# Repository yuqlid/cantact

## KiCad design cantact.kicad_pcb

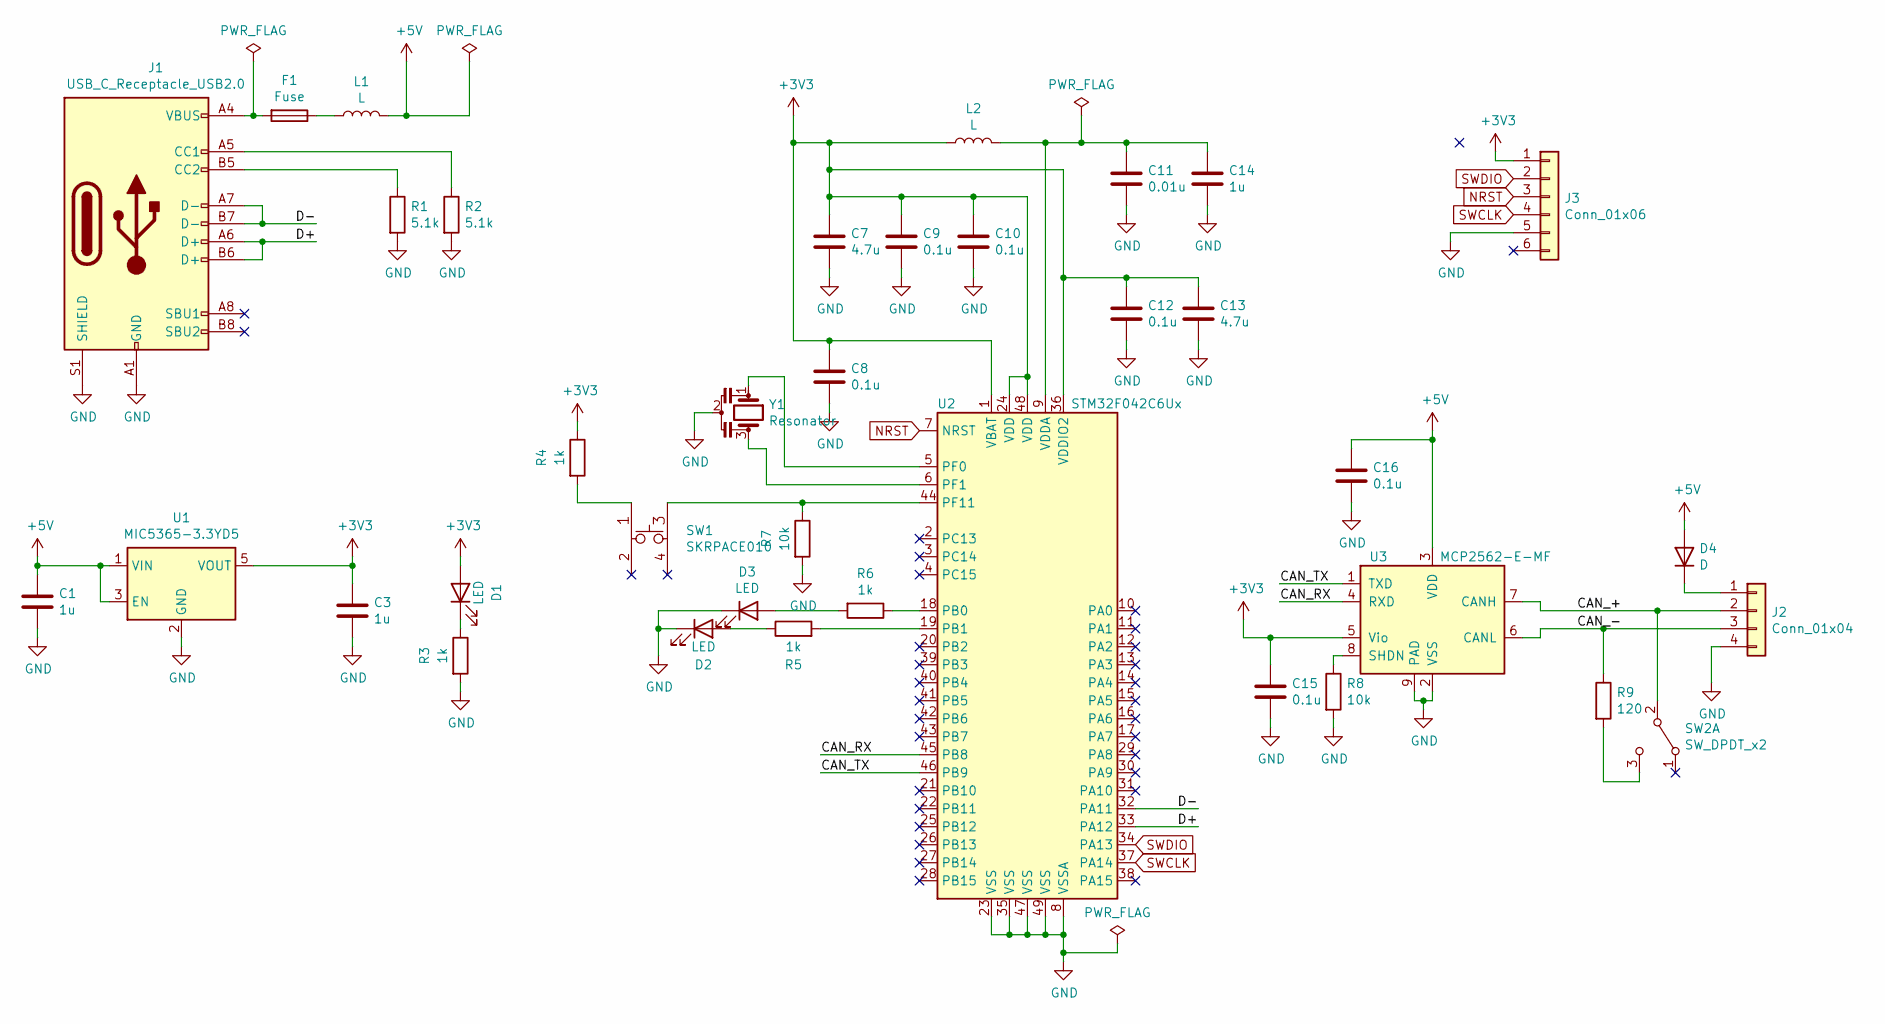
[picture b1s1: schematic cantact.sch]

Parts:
C1, C3, C14: 1u; C_0402_1005Metric
C7, C13: 4.7u; C_0603_1608Metric
C8, C9, C10, C12, C15, C16: 0.1u; C_0402_1005Metric
C11: 0.01u; C_0402_1005Metric
D1, D2, D3: LED; LED_0603_1608Metric
D4: D; D_SOD-123
F1: Fuse; Fuse_0603_1608Metric
J1: USB_C_Receptacle_USB2.0; USB_C_Receptacle_GCT_USB4085
J2: Conn_01x04; PinHeader_1x04_P2.54mm_Horizontal
J3: Conn_01x06; Tag-Connect_TC2030-IDC-NL_2x03_P1.27mm_Vertical
L1, L2: L; L_0402_1005Metric
R1, R2: 5.1k; R_0402_1005Metric
R3, R4, R5, R6: 1k; R_0402_1005Metric
R7, R8: 10k; R_0402_1005Metric
R9: 120; R_0603_1608Metric
SW1: SKRPACE010; ALPS_SKRPAxE010
SW2: SW_DPDT_x2; SW_SPDT_PCM12
U1: MIC5365-3.3YD5; SOT-23-5
U2: STM32F042C6Ux; QFN-48-1EP_7x7mm_P0.5mm_EP5.6x5.6mm
U3: MCP2562-E-MF; DFN-8-1EP_3x3mm_P0.65mm_EP1.55x2.4mm
Y1: Resonator; Resonator_SMD_muRata_CSTxExxV-3Pin_3.0x1.1mm

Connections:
+3V3: C3.1, C7.1, C8.1, C9.1, C10.1, C12.1, C13.1, C15.1, D1.2 (A), J3.1, L2.1, R4.1, U1.5 (VOUT), U2.1 (VBAT), U2.24 (VDD), U2.36 (VDDIO2), U2.48 (VDD), U3.5 (Vio)
+5V: C1.1, C16.1, D4.2 (A), L1.2, U1.1 (VIN), U1.3 (EN), U3.3 (VDD)
/CAN_+: J2.2, SW2.2 (B), U3.7 (CANH)
/CAN_-: J2.3, R9.1, U3.6 (CANL)
/CAN_RX: U2.45 (PB8), U3.4 (RXD)
/CAN_TX: U2.46 (PB9), U3.1 (TXD)
/D+: J1.A6 (D+), J1.B6 (D+), U2.33 (PA12)
/D-: J1.A7 (D-), J1.B7 (D-), U2.32 (PA11)
GND: C1.2, C3.2, C7.2, C8.2, C9.2, C10.2, C11.2, C12.2, C13.2, C14.2, C15.2, C16.2, D2.1 (K), D3.1 (K), J1.A1 (GND), J1.A12 (GND), J1.B1 (GND), J1.B12 (GND), J1.S1 (SHIELD), J2.4, J3.5, R1.2, R2.2, R3.2, R7.2, R8.2, U1.2 (GND), U2.8 (VSSA), U2.23 (VSS), U2.35 (VSS), U2.47 (VSS), U2.49 (VSS), U3.2 (VSS), U3.9 (PAD), Y1.2
NRST: J3.3, U2.7 (NRST)
unnamed: C11.1, C14.1, L2.2, U2.9 (VDDA)
unnamed: D1.1 (K), R3.1
unnamed: D2.2 (A), R5.1
unnamed: D3.2 (A), R6.2
unnamed: D4.1 (K), J2.1
unnamed: F1.1, L1.1
unnamed: F1.2, J1.A4 (VBUS), J1.A9 (VBUS), J1.B4 (VBUS), J1.B9 (VBUS)
unnamed: J1.A5 (CC1), R2.1
unnamed: J1.B5 (CC2), R1.1
unnamed: R4.2, SW1.1
unnamed: R5.2, U2.19 (PB1)
unnamed: R6.1, U2.18 (PB0)
unnamed: R7.1, SW1.3, U2.44 (PF11)
unnamed: R8.1, U3.8 (SHDN)
unnamed: R9.2, SW2.3 (C)
unnamed: U2.5 (PF0), Y1.1
unnamed: U2.6 (PF1), Y1.3
SWCLK: J3.4, U2.37 (PA14)
SWDIO: J3.2, U2.34 (PA13)

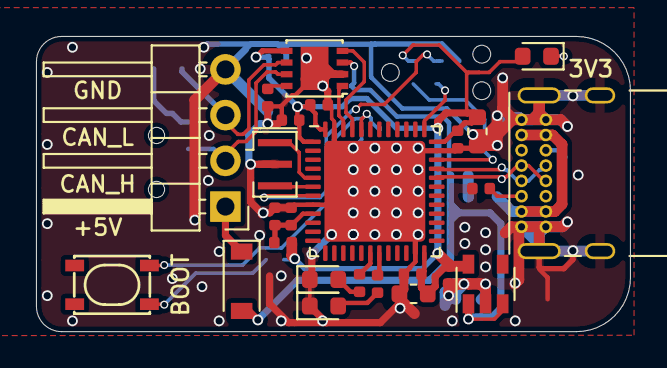
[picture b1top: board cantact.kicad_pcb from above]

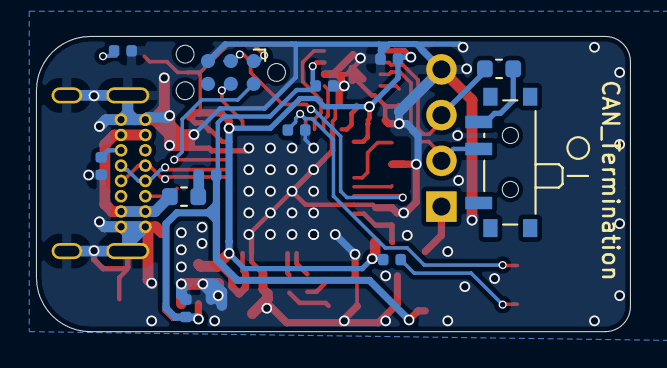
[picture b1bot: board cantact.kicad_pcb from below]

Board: 2 copper layers, 33.0 x 16.4 mm, 37 parts (12 on the bottom side), 29 nets.

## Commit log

2020-11-17 電源LEDの配置いじった
2020-12-04 不要なシルクは全部非表示にした
